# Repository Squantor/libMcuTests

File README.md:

# libMcu tests repository
This repository contains examples and tests for the [libMcu](https://github.com/Squantor/libMcu.git) library. 
This is code meant for usage in a CI/CD pipeline with a HIL (Hardware in the loop) setup I am working on. The tests are subdivided into three main parts:
* libMcuLL low level library tests with HIL setup
* libMcuHal tests, usually can run on PC
* libMcuDrivers tests, these are usually done in a HIL setup with a few boards that get rotated every while.
# Cloning
use ```git clone --recurse-submodules https://github.com/Squantor/$(PROJECT).git``` to clone the repository and its submodules. Be aware I use ssh style clones, anonymous clones might not work.
# Usage
See [firmware](firmware/README.md)

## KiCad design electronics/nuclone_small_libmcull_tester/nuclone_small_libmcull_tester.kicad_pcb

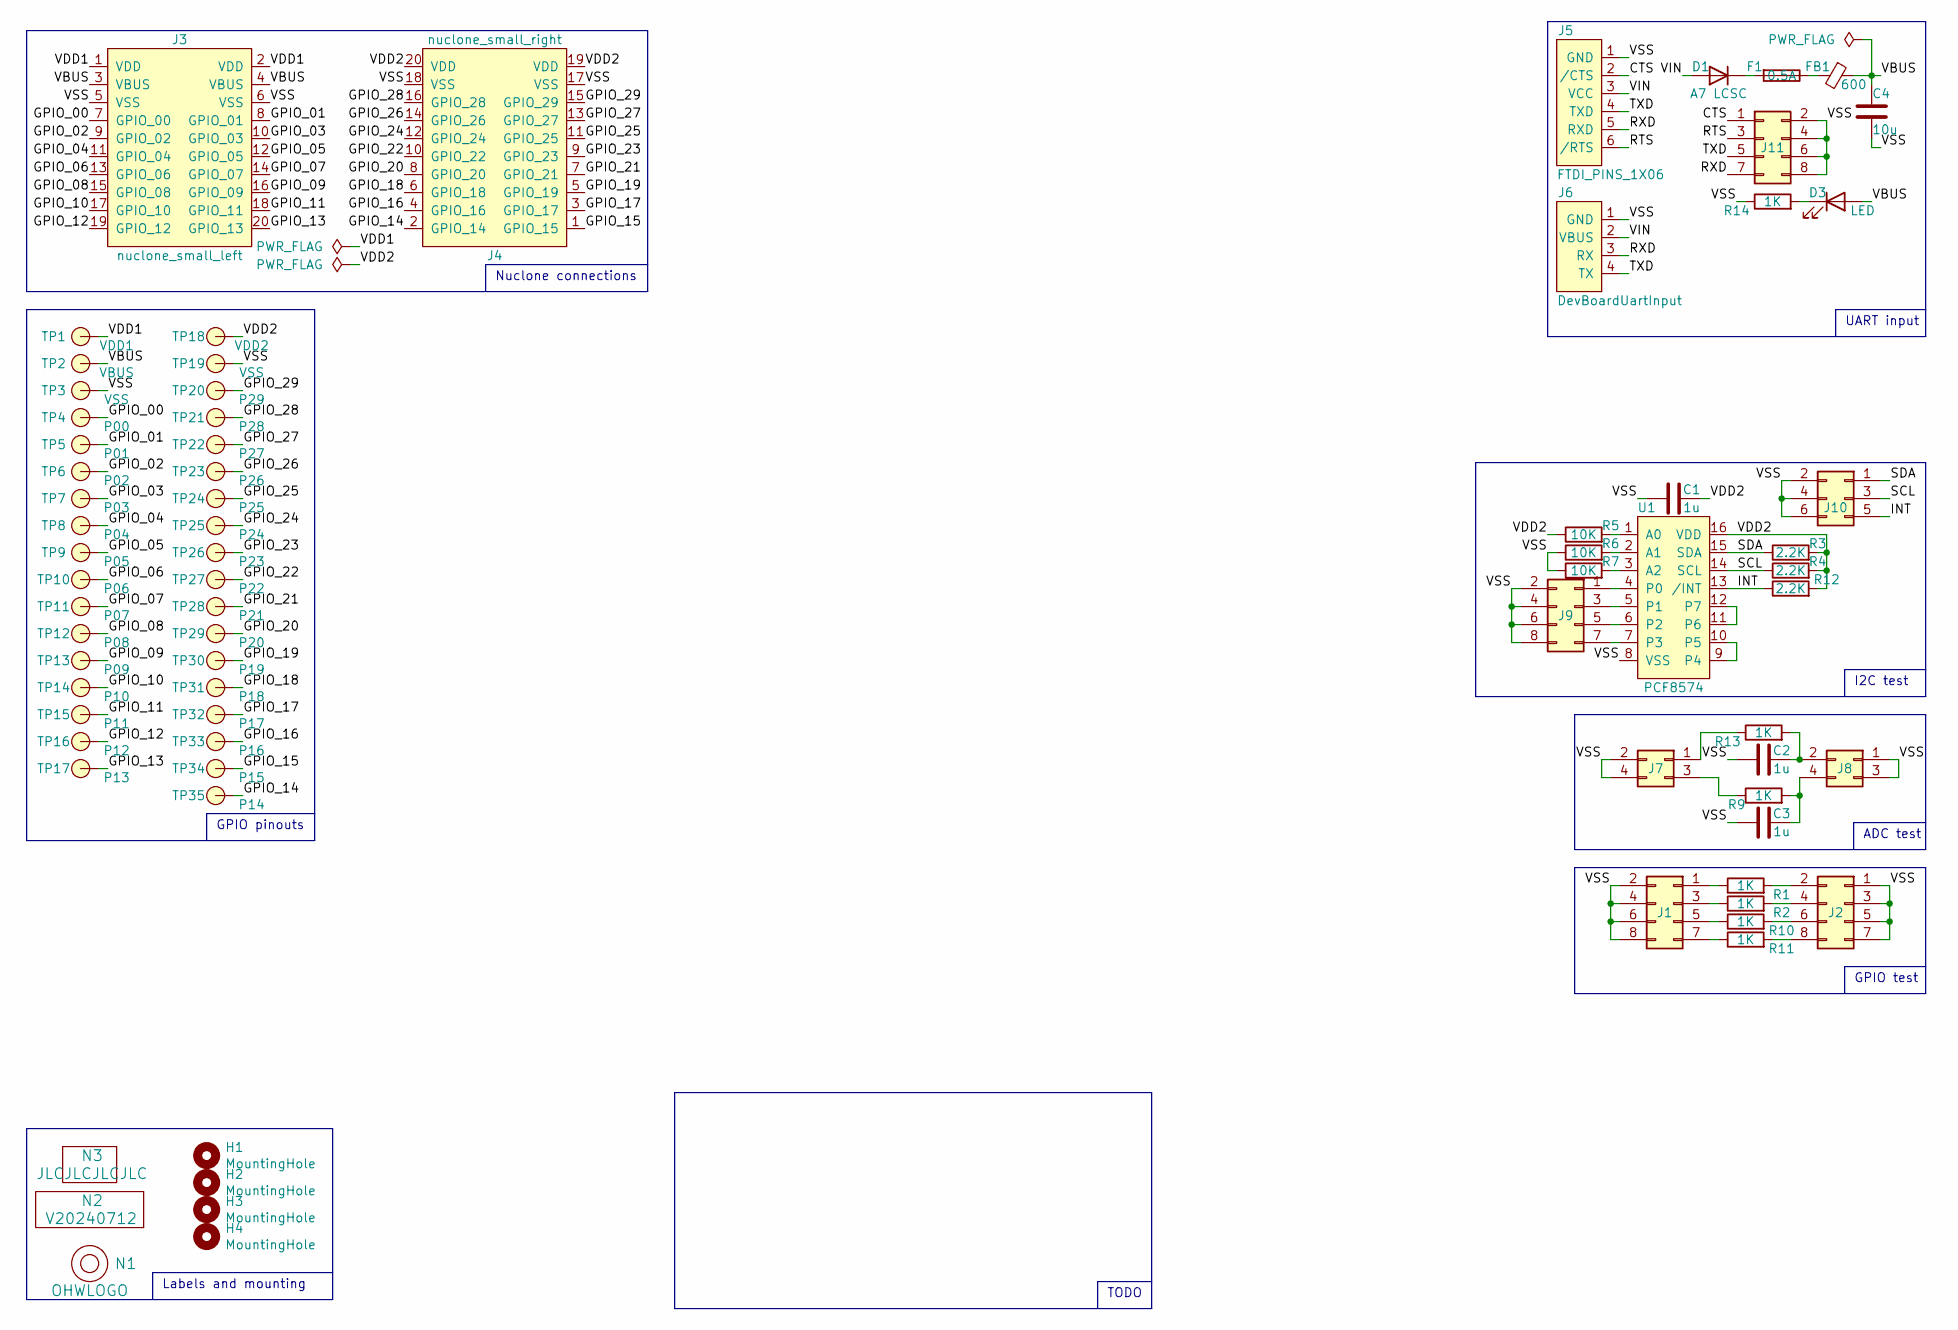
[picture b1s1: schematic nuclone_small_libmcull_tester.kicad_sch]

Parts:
C1: 1u; C_0603
C2, C3: 1u; C_0805+0603
C4: 10u; C_0603
D1: A7 LCSC; SOD-123F-hand
D3: LED; LED_0603_hand
F1: 0.5A; F_0603_hand
FB1: 600; L_0603
H1, H2, H3, H4: MountingHole; MountingHole_3.2mm_M3_Pad_Via
J1, J2, J9, J11: Conn_02x04_Odd_Even; Header-0254-2X04-H010
J3: nuclone_small_left; nuclone_small_left_stacked
J4: nuclone_small_right; nuclone_small_right_stacked
J5: FTDI_PINS_1X06; Header-0254-1X06-H010
J6: DevBoardUartInput; JST_PH_B4B-PH-K_1x04_P2.00mm_Vertical
J7, J8: Conn_02x02_Odd_Even; Header-0254-2X02-H010
J10: Conn_02x03_Odd_Even; Header-0254-2X03-H010
N1: OHWLOGO; OSHW-Symbol_6.7x6mm_SilkScreen
N2: V20240712; Label_Generic
N3: JLCJLCJLCJLC; Label_Generic
R1, R2, R9, R10, R11, R13: 1K; R_0805+0603
R3, R4, R12: 2.2K; R_0603_hand
R5, R6, R7: 10K; R_0603_hand
R14: 1K; R_0603_hand
TP1: VDD1; TestPoint_hole_H05R10_2side
TP2: VBUS; TestPoint_hole_H05R10_2side
TP3, TP19: VSS; TestPoint_hole_H05R10_2side
TP4: P00; TestPoint_hole_H05R10_2side
TP5: P01; TestPoint_hole_H05R10_2side
TP6: P02; TestPoint_hole_H05R10_2side
TP7: P03; TestPoint_hole_H05R10_2side
TP8: P04; TestPoint_hole_H05R10_2side
TP9: P05; TestPoint_hole_H05R10_2side
TP10: P06; TestPoint_hole_H05R10_2side
TP11: P07; TestPoint_hole_H05R10_2side
TP12: P08; TestPoint_hole_H05R10_2side
TP13: P09; TestPoint_hole_H05R10_2side
TP14: P10; TestPoint_hole_H05R10_2side
TP15: P11; TestPoint_hole_H05R10_2side
TP16: P12; TestPoint_hole_H05R10_2side
TP17: P13; TestPoint_hole_H05R10_2side
TP18: VDD2; TestPoint_hole_H05R10_2side
TP20: P29; TestPoint_hole_H05R10_2side
TP21: P28; TestPoint_hole_H05R10_2side
TP22: P27; TestPoint_hole_H05R10_2side
TP23: P26; TestPoint_hole_H05R10_2side
TP24: P25; TestPoint_hole_H05R10_2side
TP25: P24; TestPoint_hole_H05R10_2side
TP26: P23; TestPoint_hole_H05R10_2side
TP27: P22; TestPoint_hole_H05R10_2side
TP28: P21; TestPoint_hole_H05R10_2side
TP29: P20; TestPoint_hole_H05R10_2side
TP30: P19; TestPoint_hole_H05R10_2side
TP31: P18; TestPoint_hole_H05R10_2side
TP32: P17; TestPoint_hole_H05R10_2side
TP33: P16; TestPoint_hole_H05R10_2side
TP34: P15; TestPoint_hole_H05R10_2side
TP35: P14; TestPoint_hole_H05R10_2side
U1: PCF8574; SOIC-16W_7.5x10.3mm_P1.27mm

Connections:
/CTS: J5.2 (/CTS), J11.1
/GPIO_00: J3.7 (GPIO_00), TP4.1
/GPIO_01: J3.8 (GPIO_01), TP5.1
/GPIO_02: J3.9 (GPIO_02), TP6.1
/GPIO_03: J3.10 (GPIO_03), TP7.1
/GPIO_04: J3.11 (GPIO_04), TP8.1
/GPIO_05: J3.12 (GPIO_05), TP9.1
/GPIO_06: J3.13 (GPIO_06), TP10.1
/GPIO_07: J3.14 (GPIO_07), TP11.1
/GPIO_08: J3.15 (GPIO_08), TP12.1
/GPIO_09: J3.16 (GPIO_09), TP13.1
/GPIO_10: J3.17 (GPIO_10), TP14.1
/GPIO_11: J3.18 (GPIO_11), TP15.1
/GPIO_12: J3.19 (GPIO_12), TP16.1
/GPIO_13: J3.20 (GPIO_13), TP17.1
/GPIO_14: J4.2 (GPIO_14), TP35.1
/GPIO_15: J4.1 (GPIO_15), TP34.1
/GPIO_16: J4.4 (GPIO_16), TP33.1
/GPIO_17: J4.3 (GPIO_17), TP32.1
/GPIO_18: J4.6 (GPIO_18), TP31.1
/GPIO_19: J4.5 (GPIO_19), TP30.1
/GPIO_20: J4.8 (GPIO_20), TP29.1
/GPIO_21: J4.7 (GPIO_21), TP28.1
/GPIO_22: J4.10 (GPIO_22), TP27.1
/GPIO_23: J4.9 (GPIO_23), TP26.1
/GPIO_24: J4.12 (GPIO_24), TP25.1
/GPIO_25: J4.11 (GPIO_25), TP24.1
/GPIO_26: J4.14 (GPIO_26), TP23.1
/GPIO_27: J4.13 (GPIO_27), TP22.1
/GPIO_28: J4.16 (GPIO_28), TP21.1
/GPIO_29: J4.15 (GPIO_29), TP20.1
/INT: J10.5, R12.1, U1.13 (/INT)
/RTS: J5.6 (/RTS), J11.3
/RXD: J5.5 (RXD), J6.3 (RX), J11.7
/SCL: J10.3, R4.1, U1.14 (SCL)
/SDA: J10.1, R3.1, U1.15 (SDA)
/TXD: J5.4 (TXD), J6.4 (TX), J11.5
/VBUS: C4.1, D3.2 (A), FB1.1, J3.3 (VBUS), J3.4 (VBUS), TP2.1
/VDD1: J3.1 (VDD), J3.2 (VDD), TP1.1
/VDD2: C1.2, J4.19 (VDD), J4.20 (VDD), R3.2, R4.2, R5.1, R12.2, TP18.1, U1.16 (VDD)
/VIN: D1.2 (A), J5.3 (VCC), J6.2 (VBUS)
/VSS: C1.1, C2.1, C3.1, C4.2, J1.2, J1.4, J1.6, J1.8, J2.1, J2.3, J2.5, J2.7, J3.5 (VSS), J3.6 (VSS), J4.17 (VSS), J4.18 (VSS), J5.1 (GND), J6.1 (GND), J7.2, J7.4, J8.1, J8.3, J9.2, J9.4, J9.6, J9.8, J10.2, J10.4, J10.6, J11.2, J11.4, J11.6, J11.8, R6.1, R7.1, R14.1, TP3.1, TP19.1, U1.8 (VSS)
unnamed: D1.1 (K), F1.2
unnamed: D3.1 (K), R14.2
unnamed: F1.1, FB1.2
unnamed: J1.1, R1.1
unnamed: J1.3, R2.1
unnamed: J1.5, R10.1
unnamed: J1.7, R11.1
unnamed: J2.2, R1.2
unnamed: J2.4, R2.2
unnamed: J2.6, R10.2
unnamed: J2.8, R11.2
unnamed: J7.1, R13.1
unnamed: J7.3, R9.1
unnamed: C2.2, J8.2, R13.2
unnamed: C3.2, J8.4, R9.2
unnamed: J9.1, U1.4 (P0)
unnamed: J9.3, U1.5 (P1)
unnamed: J9.5, U1.6 (P2)
unnamed: J9.7, U1.7 (P3)
unnamed: R5.2, U1.1 (A0)
unnamed: R6.2, U1.2 (A1)
unnamed: R7.2, U1.3 (A2)
unnamed: U1.9 (P4), U1.10 (P5)
unnamed: U1.11 (P6), U1.12 (P7)

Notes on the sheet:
I2C test
GPIO test
Labels and mounting
TODO
GPIO pinouts
Nuclone connections
UART input
ADC test

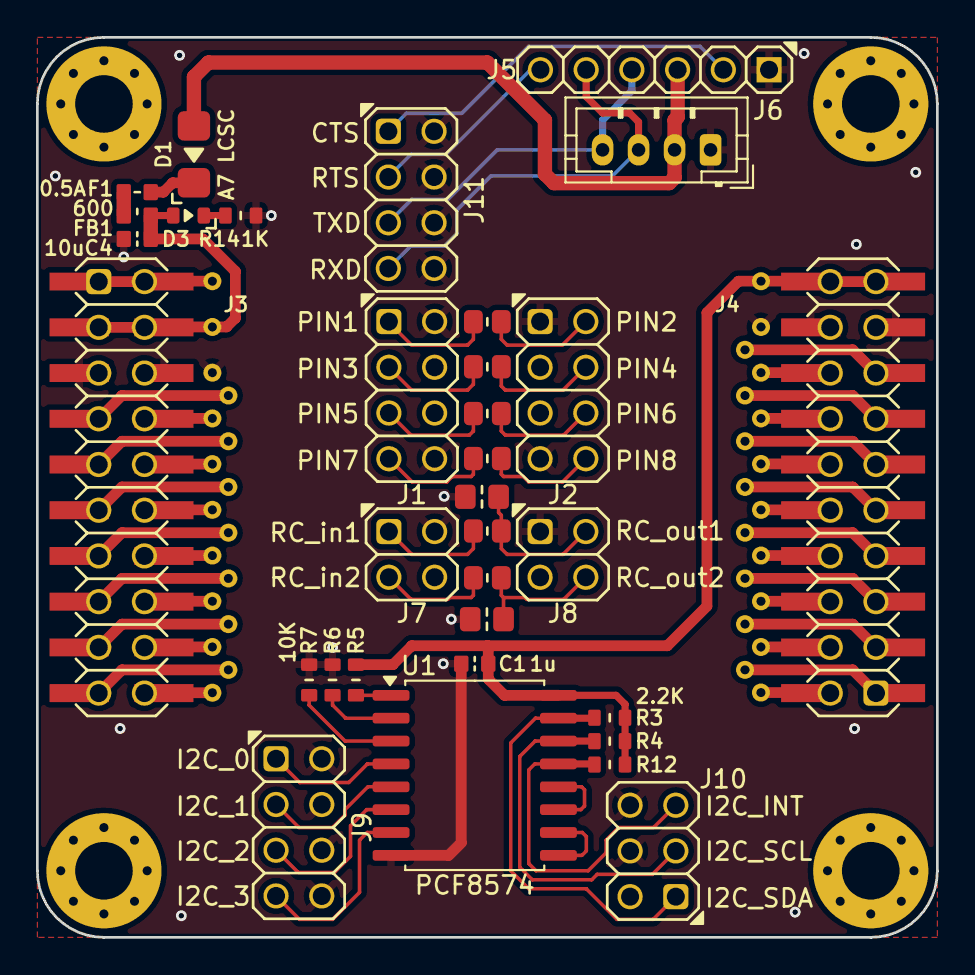
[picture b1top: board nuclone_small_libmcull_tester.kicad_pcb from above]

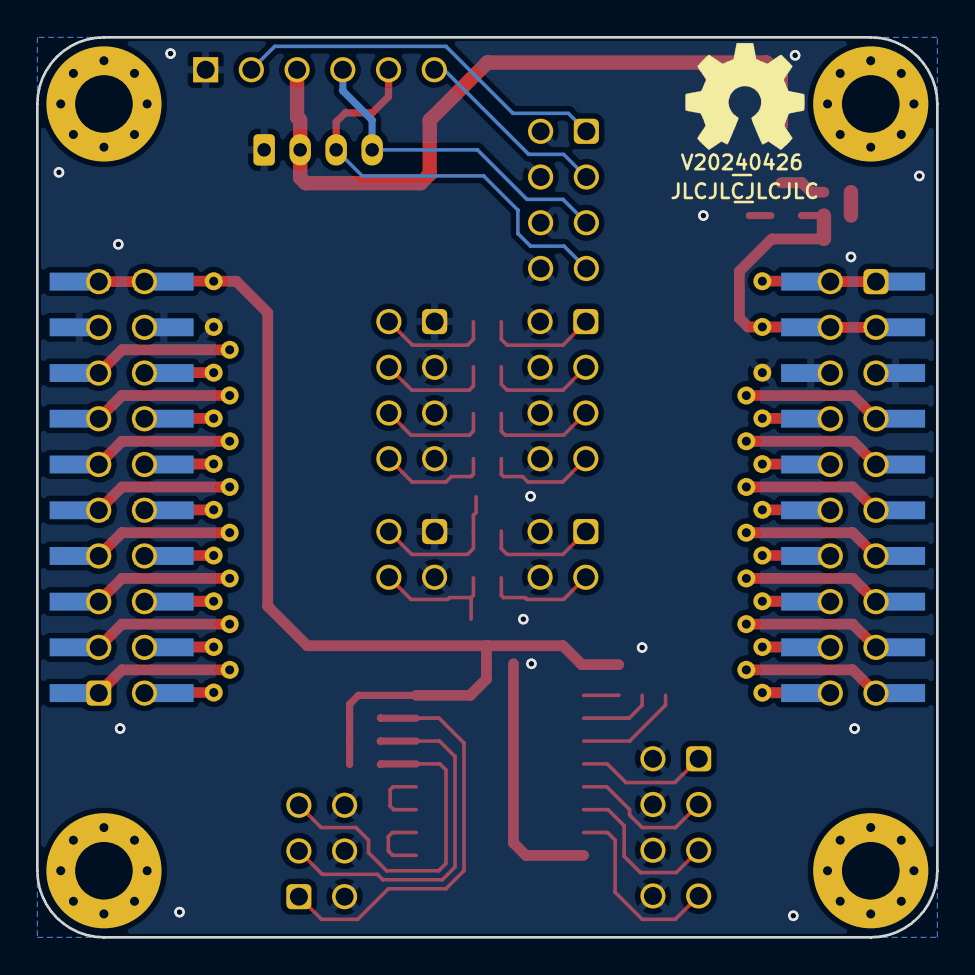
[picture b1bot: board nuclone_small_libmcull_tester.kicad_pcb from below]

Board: 2 copper layers, 50.0 x 50.0 mm, 75 parts (3 on the bottom side), 66 nets.

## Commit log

2024-02-23 populating repo with stuff from libMcuLLexamples
2024-02-23 updated readme's with bit more then placeholder data
2024-03-01 WIP rename actions
2024-03-01 renamed all projects in vscode
2024-03-01 supress warning
2024-03-01 more renames
2024-03-01 renamed vscode targets
2024-03-01 moving and renaming, some changes
2024-03-01 compiling LPC845 tests
2024-03-01 updated and cut down files to have a barebones implementation
2024-03-08 started with RP2040 tests
2024-03-08 added CRC's for various flash chip bootloaders
2024-03-08 removed old defunct debugging script and added RP2040 debugging
2024-03-08 WIP RP2040 GPIO tests
2024-03-08 added HSI information
2024-03-15 updated library
2024-03-17 newer library
2024-04-01 updated lib
2024-04-08 updated submodule, few extra commits
2024-04-15 starting with initializing the nuclone board
2024-04-15 testing if the LED turns on (it does)
2024-04-16 added peripheral resets
2024-04-22 moved small nuclone libmcull tester
2024-04-22 updated footprints and versionnumber
2024-04-25 connected up LED pin to test a blinky
2024-04-26 added additional gpio types
2024-04-26 added gpio pin muxing tests
2024-04-26 added pads tests
2024-04-26 adding some bits to teardown
2024-04-26 added GPIO tests
2024-04-26 small fixes, preparing for production
2024-05-03 updated libraries
2024-05-03 porting to different include structure
2024-05-03 switching to hal
2024-05-03 refactoring of io name, starting using usings by the LL library
2024-05-06 added HAL tests
2024-05-06 differentiating LL and HAL nuclone tests, added tests
2024-05-06 completed HAL pins tests
2024-05-07 starting with HAL tests
2024-05-07 WIP HAL gpio tests
2024-05-08 completed tests
2024-05-08 first driver test project
2024-05-08 experimenting with trait template passing
2024-05-14 completed tests for RP2040 3to8 mux
2024-05-14 updated library, added GDB scripts
2024-05-15 reverting some HAL experiments in the LL test project
2024-05-16 started with LL SPI tests
2024-05-17 WIP crystal oscillator operation
2024-05-17 initialzing clock out and PLL
2024-05-21 now full speed clocking available
2024-05-24 applying some namespace refactoring
2024-05-24 fixed LPC845 after namespace refactoring
2024-05-24 using some predefined types, splitting SPI tests into setup and comms checks
2024-05-24 added spi tests for setup in motorola format
2024-05-24 readwrite test works, now need to test read
2024-05-27 started with i2c tests
2024-05-27 adding instance of I2C peripheral
2024-05-27 small updates
2024-05-31 brace initialization update for LPC8X
2024-05-31 DONE: I2C setup
2024-05-31 WIP I2C write tests
2024-06-03 testing transmit with error handling and timeouts
2024-06-03 receive tests working
2024-06-03 added i2c read/write loop refactor
2024-06-03 change of handling
2024-06-04 added empty test files
2024-06-04 renamed to clarify what is LL tests and what are HAL tests
2024-06-04 added uart stuff, WIP uart setup tests
2024-06-05 added baud rate tests
2024-06-06 working uart read/write
2024-06-21 updating LPC845 test program
2024-06-21 moving around some projects
2024-06-21 all projects build again
2024-06-21 make it possible to debug LPC845
2024-07-05 starting with clock setup functionality
2024-07-05 added numbering of test gpio's
2024-07-12 preparation for production
2024-07-14 try out clock output selection
2024-07-14 switched main clock to use crystal oscillator
2024-07-19 PLL works, CPU running at 30MHz
2024-07-19 started with some pin definitions
2024-07-26 updated to kicad 8
2024-08-02 small project updates
2024-08-02 added pin definitions
2024-08-02 added more tests to LPC845
2024-08-02 usart tests
2024-09-16 added ringbuffer tests for libmcu
2024-09-16 updated to different libmcu include structure
2024-10-04 updated to new namespace standard
2024-10-04 LPC812 now compiles again
2024-10-06 namespace refactoring part 1
2024-10-06 refactoring actions
2024-10-11 fixed rp2040 hal tests
2024-10-12 added bunch of new test projects
2024-10-12 STM32F031K6T compiles but no libmcull just yet
2024-10-12 renamed target files to different structure
2024-10-13 able to launch STM32F031 test project
2024-10-13 updated library and launch
2024-10-18 clock configuration API update
2024-10-18 removed division routine rom forwarding
2024-10-18 added delays to iocon so those tests dont fail, updated uart to clocking API
2024-10-18 updated API and loose ends
2024-10-19 libmcu rename, updated target versionnumber, removed old project from build.sh
2024-10-19 adapted to newer clocking API
2024-10-21 small updates to clocking
2024-10-25 updated clocking API for LPC845
2024-11-01 some work on STM32F031 tests
2024-11-08 WIP gpio STM32F031
2024-12-08 copied over bitblit tests
2024-12-08 adapted tests to refactored code
2024-12-13 WIP tests for multi bit width templated bitblit
2024-12-14 starting again with different bitblit API
2024-12-29 moving around tests and splitting tests for various cases
2024-12-29 tests for equal datasize bitblit
2025-02-21 updated to library API updates
2025-02-21 Started with DMA test implementation, WIP init test
2025-02-21 working dma init test
2025-02-28 working memory to memory transfers
2025-03-07 working memory to peripheral dma test, using uart DMA
2025-03-14 tests for DMA memory to peripheral and peripheral to memory
2025-03-21 shimmed HAL test for uart Init
2025-03-21 library update
2025-03-28 every project builds again
2025-03-28 everything builds now with all the renames going on
2025-04-04 updated to different naming conventions
2025-04-11 WIP renames to adhere to google standard
2025-04-18 updates after refactoring
2025-05-02 WIP changing of naming to google standard
2025-05-27 renames after refactoring
2025-05-28 WIP rename actions to google naming standard
2025-05-29 WIP rename to google standard
2025-05-30 Updated with newer HAL functionality
2025-06-06 WIP refactoring to google naming convention
2025-06-06 Started with LPC845 polled SPI
2025-06-08 WIP completed refactoring for NXP
2025-06-09 updated to google naming conventions
2025-06-13 some renames and RP2040 HAL GPIO tests for new API
2025-06-14 fixed after gpio/mux refactor
2025-06-14 updated to newer library version with additional concepts
2025-06-20 renames due to refactoring
2025-06-27 started with tests for lpc845 low level polled i2c class
2025-06-27 basic i2c transmit/receive tests
2025-06-27 added lpc845 i2c interrupt driven tests
2025-06-27 Fixed build error after refactoring nvic
2025-06-28 fixed tests for reception
2025-07-04 refactoring of k prefixes
2025-07-11 refactoring updates
2025-07-25 small refactoring
2025-07-25 added tests for LPC845 I2C interrupt HAL
2025-07-25 removed all k prefixes from constants
2025-07-25 preparation for Low Level interrupt driven Uart
2025-08-19 Made LPC845 Low Level interrupt driven USART tests for initialisations and asynchronous claim interface
2025-08-20 added tests for interrupt driven transmit and receive methods
2025-09-05 added interrupt driven uart hal tests
2025-09-05 changed uart api to not use handles
2025-11-28 fixed potential issue with the Makefile
2025-11-28 updated project to newer kicad version
2025-11-28 fixed compilation errors due to API changes, tests now with callbacks
2025-11-28 tests for multi transfer API
2025-12-04 Fixed build error due to API changes
2025-12-04 WIP fixing API changes
2025-12-05 updated tests
2025-12-05 Updated HAL tests with different API without handles/claiming, updated LL tests to not have Stop but StopTransmit/StopReceive
2025-12-05 created tests for exercising queue handling
2025-12-06 added tests on for queue processing on target and updated PC unittests due to changed behavior
2025-12-12 updated libmcu
2025-12-12 Tests for CRTP implementation
2025-12-12 removed general prefixes from libmcu header files
2025-12-12 updates after API changes and removing old classes
2025-12-12 refactoring after rename from async to nonblocking
2025-12-12 updated to refactored libmcu
2025-12-23 added tests for ringbuffer
2025-12-23 refactored ringblockbuffer to ringallocator
2025-12-23 renamed ring allocator to fifo allocator
2025-12-23 added First in Never out allocator tests, split off utility functions
2026-02-06 refactoring to new libmcu, fixing build errors
2026-02-20 testing bitblit source size and position
2026-03-04 updated tests with new policy based assertions
2026-03-06 added tests for assert policies
2026-03-20 updated tests for FiNo allocator
2026-03-20 naming change, added FIDFO allocator tests
2026-03-20 naming refactoring
2026-05-15 updated tests after ringbuffer refactoring
2026-05-15 added test for edge conditions that had a bug
2026-05-29 removed tests for obsolete functions, added tests for mregel
2026-06-05 added clang-tidy to unittests
2026-06-05 clang-tidy fixes for local variable names to be snake_case
